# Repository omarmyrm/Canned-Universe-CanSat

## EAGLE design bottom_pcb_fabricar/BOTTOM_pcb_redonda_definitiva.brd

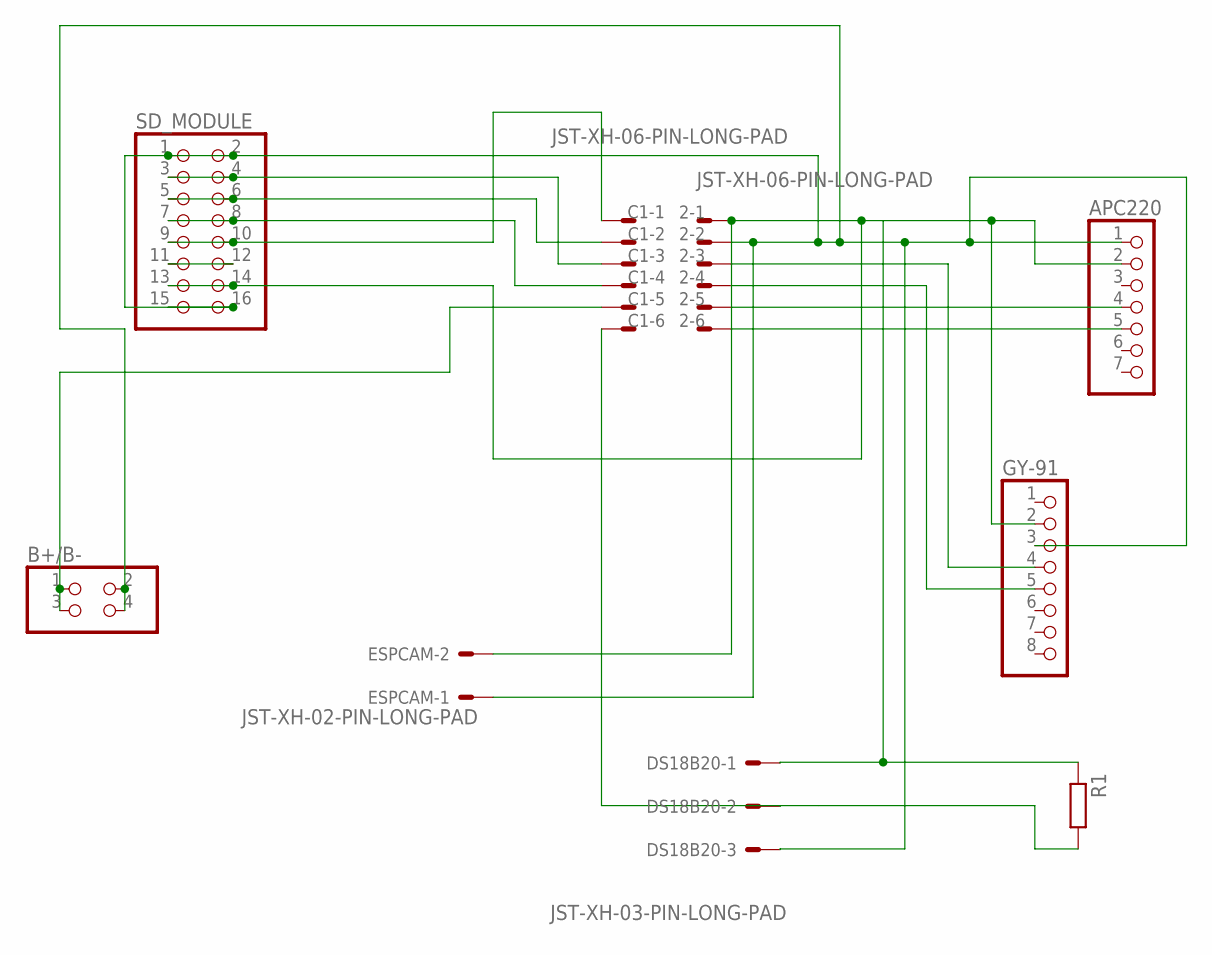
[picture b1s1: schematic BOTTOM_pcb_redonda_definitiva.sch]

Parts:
2: JST-XH-06-PIN-LONG-PAD; JST-XH-06-PACKAGE-LONG-PAD
APC220: PINHD-1X7; 1X07
B+/B-: PINHD-2X2; 2X02
C1: JST-XH-06-PIN-LONG-PAD; JST-XH-06-PACKAGE-LONG-PAD
DS18B20: JST-XH-03-PIN-LONG-PAD; JST-XH-03-PACKAGE-LONG-PAD
ESPCAM: JST-XH-02-PIN-LONG-PAD; JST-XH-02-PACKAGE-LONG-PAD
GY-91: PINHD-1X8; 1X08
R1: R-EU_0207/10; 0207/10
SD_MODULE: PINHD-2X8; 2X08

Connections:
unnamed: B+/B-.1, B+/B-.3, C1.5
unnamed: 2.2, APC220.1, B+/B-.2, B+/B-.4, DS18B20.3, ESPCAM.1, GY-91.3, SD_MODULE.1, SD_MODULE.2, SD_MODULE.15, SD_MODULE.16
unnamed: 2.5, APC220.4
unnamed: 2.6, APC220.5
unnamed: 2.3, GY-91.4
unnamed: 2.4, GY-91.5
unnamed: C1.6, DS18B20.2, R1.2
unnamed: C1.3, SD_MODULE.3, SD_MODULE.4
unnamed: C1.2, SD_MODULE.5, SD_MODULE.6
unnamed: C1.4, SD_MODULE.7, SD_MODULE.8
unnamed: C1.1, SD_MODULE.9, SD_MODULE.10
unnamed: SD_MODULE.11, SD_MODULE.12
unnamed: 2.1, APC220.2, DS18B20.1, ESPCAM.2, GY-91.2, R1.1, SD_MODULE.13, SD_MODULE.14

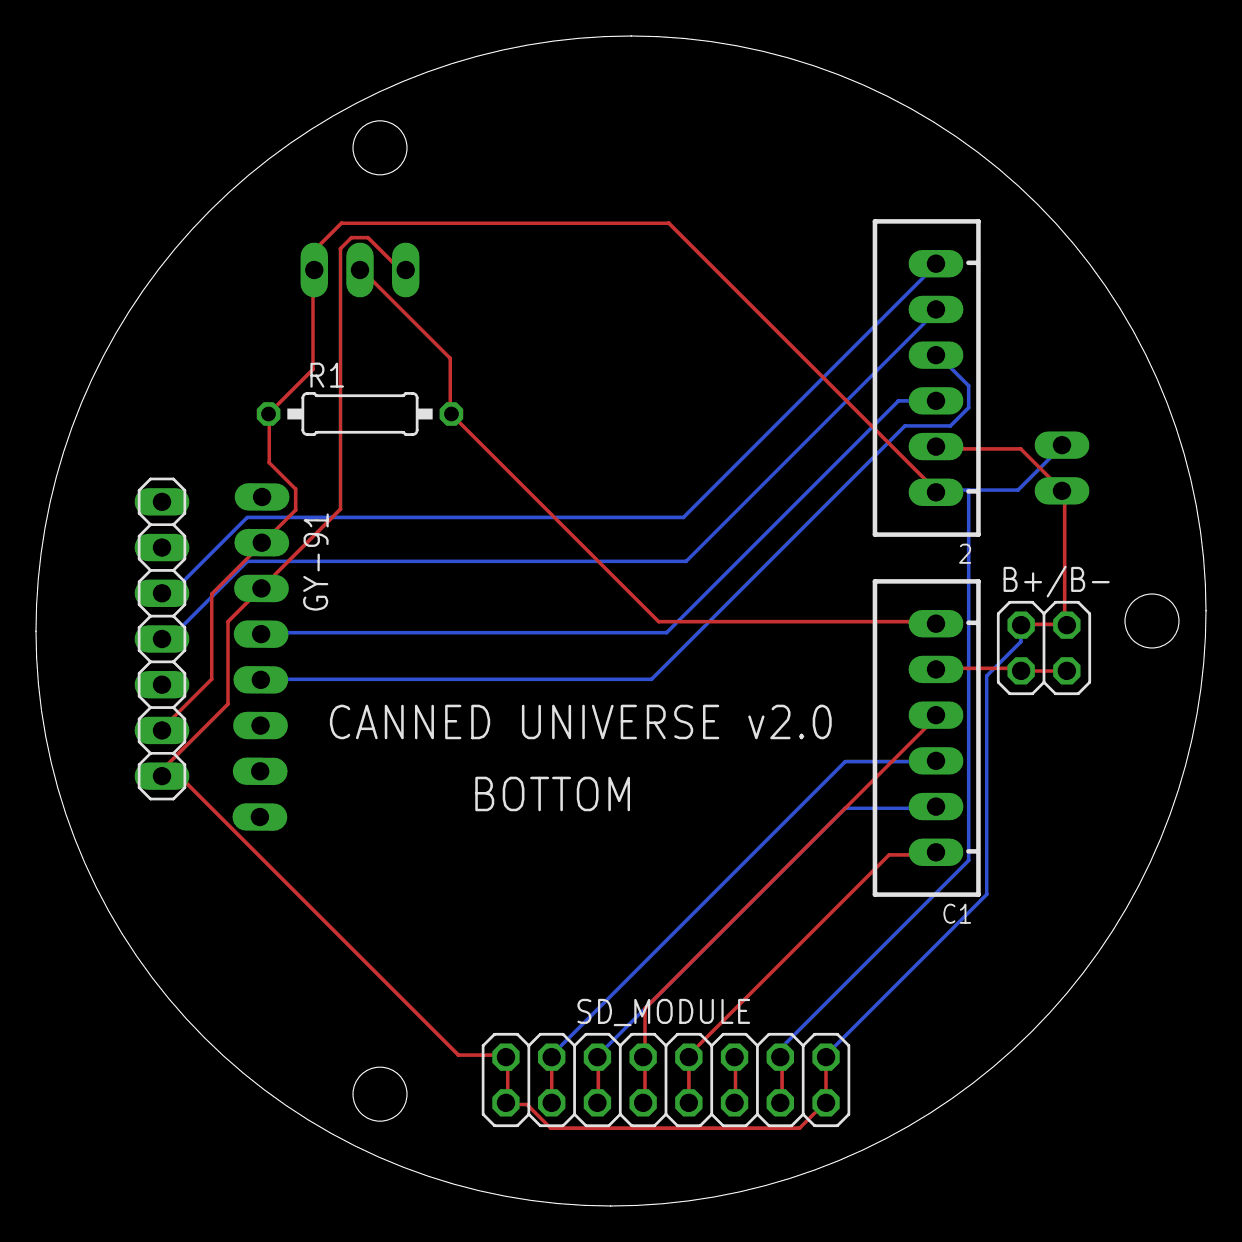
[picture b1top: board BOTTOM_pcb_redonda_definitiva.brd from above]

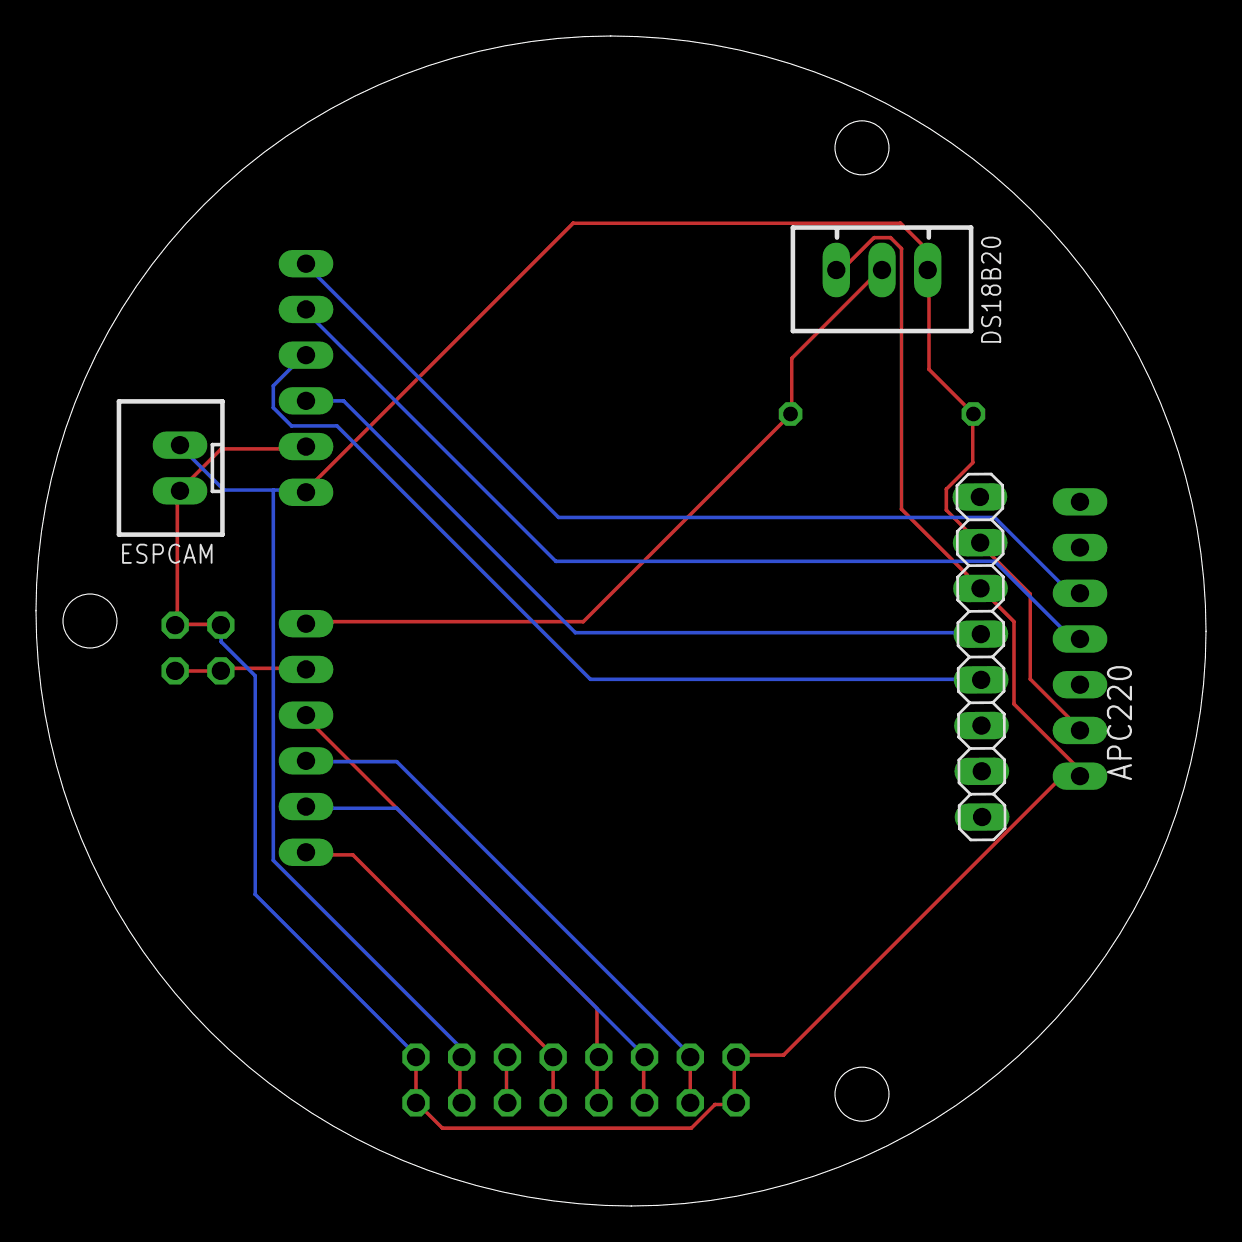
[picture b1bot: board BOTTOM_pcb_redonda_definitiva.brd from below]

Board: 2 copper layers, 65.0 x 65.0 mm, 9 parts (3 on the bottom side), 13 nets.

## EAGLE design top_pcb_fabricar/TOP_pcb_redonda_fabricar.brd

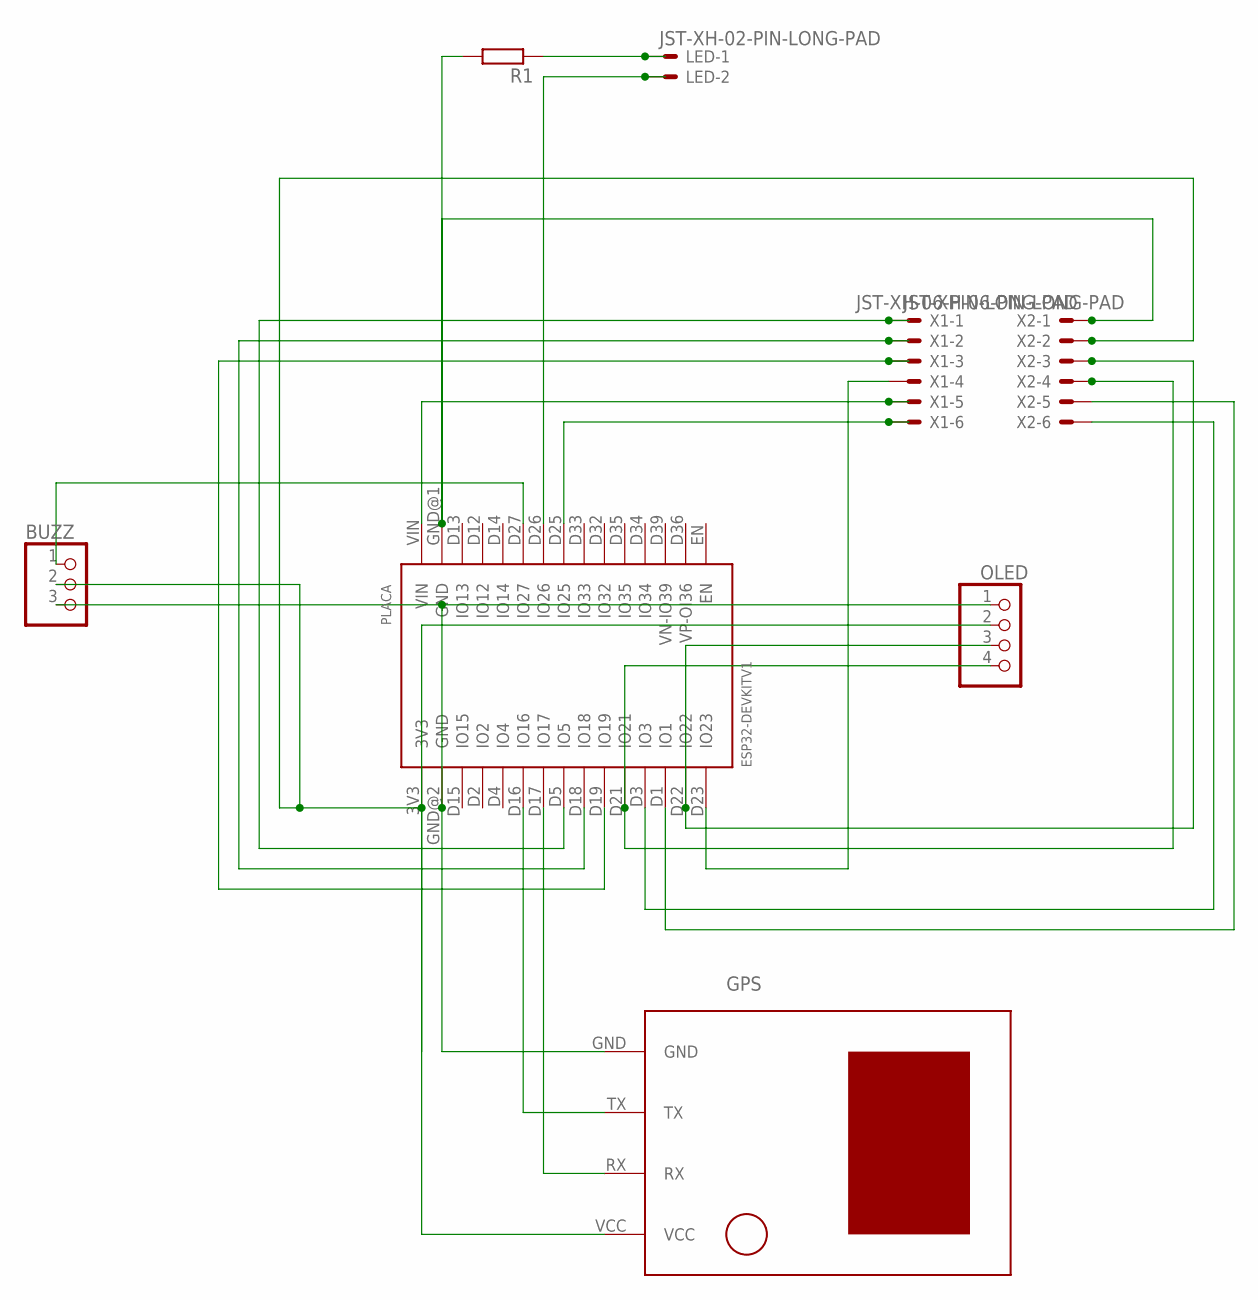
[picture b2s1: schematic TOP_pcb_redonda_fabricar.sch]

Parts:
BUZZ: PINHD-1X3; 1X03
GPS: U-BLOX-NEO6V2
LED: JST-XH-02-PIN-LONG-PAD; JST-XH-02-PACKAGE-LONG-PAD
OLED: PINHD-1X4; 1X04
PLACA: ESP32DEVKITV1; ESP32-DEVKITV1
R1: R-EU_0207/10; 0207/10
X1, X2: JST-XH-06-PIN-LONG-PAD; JST-XH-06-PACKAGE-LONG-PAD

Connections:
GPS: BUZZ.3, GPS.GND, OLED.1, PLACA.GND@2 (GND)
unnamed: BUZZ.2, GPS.VCC, OLED.2, PLACA.3V3, X2.2
unnamed: PLACA.GND@1 (GND), R1.2, X2.1
unnamed: PLACA.VIN, X1.5
unnamed: OLED.3, PLACA.D22 (IO22), X2.3
unnamed: OLED.4, PLACA.D21 (IO21), X2.4
unnamed: PLACA.D3 (IO3), X2.6
unnamed: PLACA.D1 (IO1), X2.5
unnamed: GPS.RX, PLACA.D17 (IO17)
unnamed: GPS.TX, PLACA.D16 (IO16)
unnamed: PLACA.D25 (IO25), X1.6
unnamed: LED.2, PLACA.D26 (IO26)
unnamed: LED.1, R1.1
unnamed: BUZZ.1, PLACA.D27 (IO27)
unnamed: PLACA.D18 (IO18), X1.2
unnamed: PLACA.D19 (IO19), X1.3
unnamed: PLACA.D23 (IO23), X1.4
unnamed: PLACA.D5 (IO5), X1.1

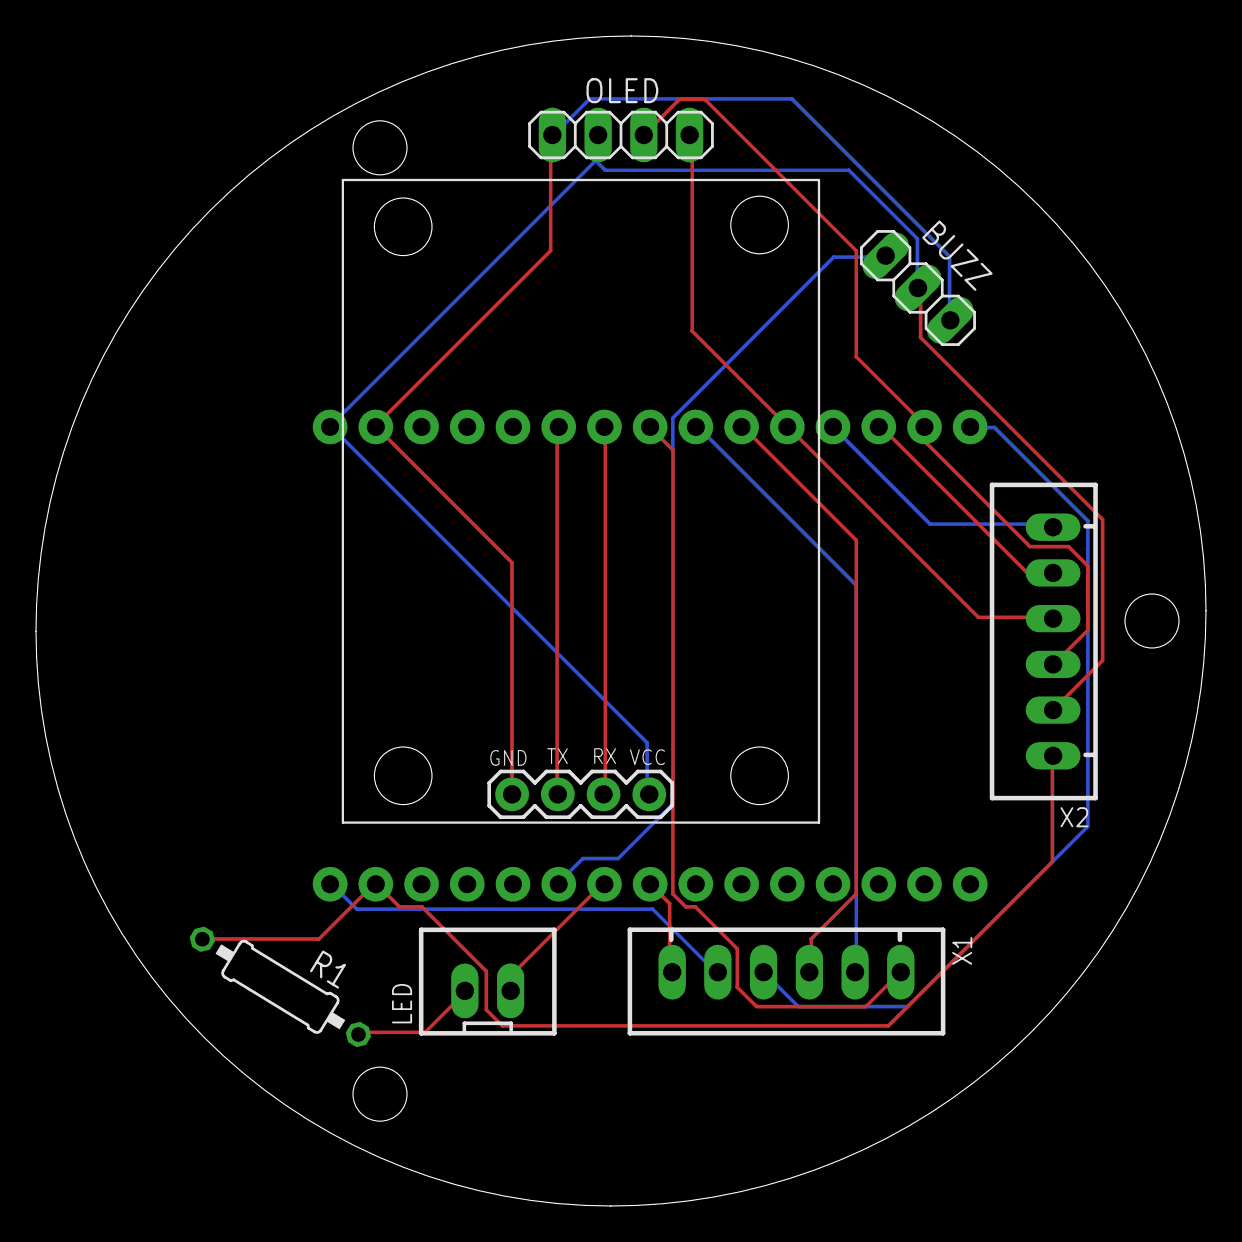
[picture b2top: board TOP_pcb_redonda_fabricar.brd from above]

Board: 2 copper layers, 65.0 x 65.0 mm, 8 parts (1 on the bottom side), 18 nets.

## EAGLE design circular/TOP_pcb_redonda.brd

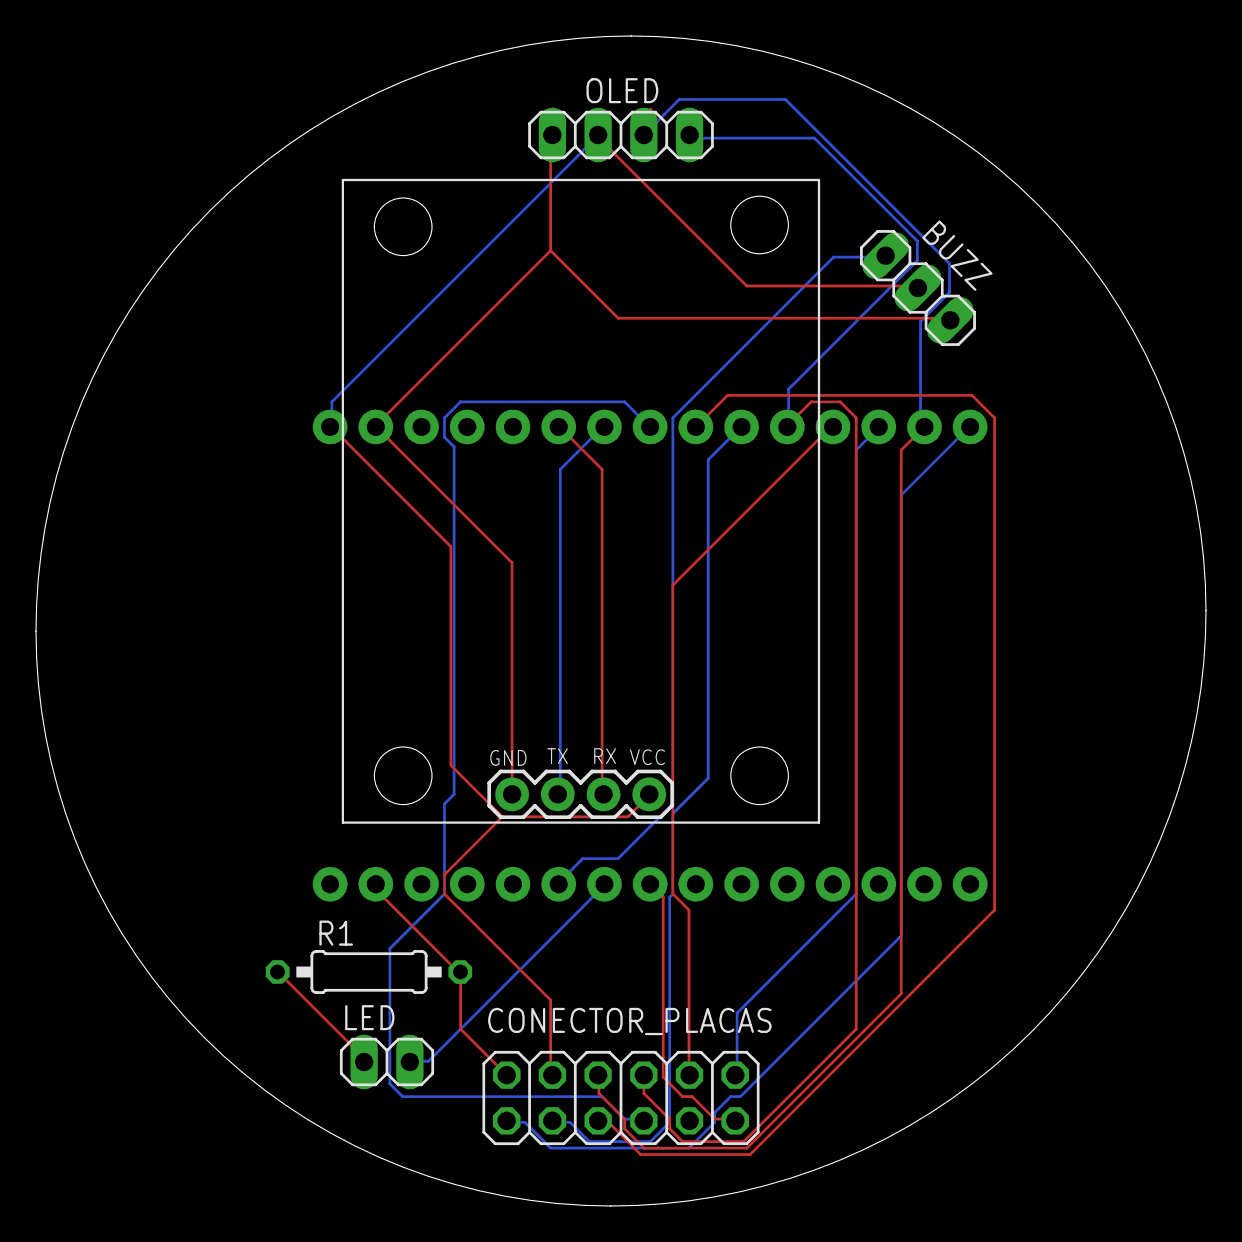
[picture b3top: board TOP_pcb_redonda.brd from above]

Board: 2 copper layers, 65.0 x 65.0 mm, 7 parts (1 on the bottom side), 17 nets.

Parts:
BUZZ: 1X03
CONECTOR_PLACAS: 2X06
GPS: U-BLOX-NEO6V2
LED: 1X02
OLED: 1X04
PLACA: ESP32DEVKITV1; ESP32-DEVKITV1
R1: 0207/10

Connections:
GPS: BUZZ.3, GPS.GND, OLED.1, PLACA.GND@2
unnamed: BUZZ.2, CONECTOR_PLACAS.4, GPS.VCC, OLED.2, PLACA.3V3
unnamed: CONECTOR_PLACAS.2, PLACA.GND@1, R1.2
unnamed: CONECTOR_PLACAS.6, OLED.3, PLACA.D22
unnamed: CONECTOR_PLACAS.8, OLED.4, PLACA.D21
unnamed: CONECTOR_PLACAS.10, PLACA.D3
unnamed: CONECTOR_PLACAS.12, PLACA.D1
unnamed: GPS.RX, PLACA.D16
unnamed: GPS.TX, PLACA.D17
unnamed: CONECTOR_PLACAS.11, PLACA.D25
unnamed: LED.2, PLACA.D26
unnamed: LED.1, R1.1
unnamed: BUZZ.1, PLACA.D27
unnamed: CONECTOR_PLACAS.1, PLACA.D23
unnamed: CONECTOR_PLACAS.3, PLACA.D19
unnamed: CONECTOR_PLACAS.5, PLACA.D18
unnamed: CONECTOR_PLACAS.7, PLACA.D5

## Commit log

2020-12-03 determinar superficie paracaídas
    Programa para determinar la superficie del paracaídas.
2021-02-02 Add files via upload
    diría que está bastante comentado para que aunque no sea el código de uno mismo se pueda entender bien. Que a veces es difícil
2021-05-27 Rename libSD.h to libSDcard.h
2021-05-27 Update DEFINITIVO.ino
    commented all the code so it's more readable
    the code should work fine
    need to add the ds18b20
2021-05-27 Update DEFINITIVO.ino
    commented all the code finally
